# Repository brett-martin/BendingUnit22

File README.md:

# Bending Unit 22

BU-22 is a modular animatronic Bender-inspired clock and character display.
The Brain orchestrates operating modes, sensors, time, audio, and user input.
Independent Eyes and Mouth controllers own their LED hardware, rendering, and
precisely timed local animations.

This repository currently contains the proven Brain/Eyes breadboard tests,
draft display protocol, experimental content catalogs, and first clean v0
CircuitPython firmware slice.

## Repository map

```text
BU22_Brain/
  firmware/v0/          First Brain protocol exerciser
  tests/                Feather smoke test and reusable I2C validation suite

BU22_Eyes/
  catalogs/             Experimental expressions, animations, performances
  firmware/v0/          First clean Eyes firmware slice
  tests/                Universal I2C receiver and hardware-test backups

BU22_Mouth/
  README.md             Mouth subsystem placeholder

protocol/
  semantic_protocol_v0.md   Behavior, terminology, and ownership
  wire_protocol_v0.md       Concrete draft I2C encoding
  commands.md               Raw breadboard-only validation bytes
```

The original six-channel electrical bring-up programs are preserved under the
named Brain and Eyes test folders rather than serving as production firmware.

## Current breadboard hardware

- Adafruit Feather RP2040 acting as Brain
- Adafruit KB2040 acting as Eyes controller
- Six independent four-pixel SK9822 strands
- Three 74AHCT125 level-shifter ICs
- Independent USB power for both MCUs during development
- External regulated 5 V for level shifters and LEDs
- Shared ground, SDA, and SCL
- 4.7k I2C pull-ups to the Brain's 3.3 V rail
- Qwiic red power conductor disconnected during independent USB testing

### Eyes channel pin map

| Channel | Data | Clock |
|---:|---:|---:|
| 1 | D2 | D3 |
| 2 | D4 | D5 |
| 3 | D6 | D7 |
| 4 | D8 | D9 |
| 5 | D10 | A0 |
| 6 | A1 | A2 |

The current test assembly is physically rotated 180 degrees. Firmware keeps
content in logical orientation and applies the hardware transform at render
time.

## Proven functionality

- I2C discovery at Eyes address `0x30`
- One-byte and parameterized multi-byte commands
- Global brightness control
- Independent six-channel and 24-pixel control
- Complete 25-byte frame streaming at 10 FPS with no late frames
- Bidirectional status readback under display traffic
- Locally stored expressions and animations
- Immediate Brain interruption and STOP
- Dedicated Visor Down/Up row transitions
- Brain and Eyes disconnect/reconnect recovery
- Five-second standalone Normal fallback
- Visible missing-content development errors
- Concise action-level Eyes serial logging

See [the I2C validation index](BU22_Brain/tests/i2c_validation/README.md)
for the reusable development-board test sequence.

## Content catalogs

Expressions, animations, and performances use separate numeric ID spaces.
They remain experimental before v1. At v1, reviewed IDs become stable; later
content is appended while existing entries may improve without changing their
semantic meaning.

See [the Eyes catalog rules](BU22_Eyes/catalogs/README.md).

## Protocol documents

- [Semantic protocol v0](protocol/semantic_protocol_v0.md)
- [Wire protocol v0](protocol/wire_protocol_v0.md)
- [Raw hardware-validation commands](protocol/commands.md)

The semantic and wire documents are drafts. The raw validation bytes remain
separate so future hardware can rerun today's proven tests regardless of how
the production protocol evolves.

## Running the v0 Brain/Eyes slice

On the KB2040 Eyes `CIRCUITPY` drive, copy:

```text
BU22_Eyes/firmware/v0/code.py
BU22_Eyes/firmware/v0/config.py
BU22_Eyes/firmware/v0/content.py
```

Its `lib` directory also needs:

```text
adafruit_dotstar.mpy
adafruit_pixelbuf.mpy
```

On the Feather RP2040 Brain `CIRCUITPY` drive, copy:

```text
BU22_Brain/firmware/v0/code.py
```

The exerciser cycles expressions and animations, interrupts an animation,
tests Off and visor transitions, requests missing animation `999`, reads the
error status, and recovers with Normal.

## CircuitPython dependencies

Install the DotStar CircuitPython dependencies with:

```sh
python3 -m circup install -r requirements.txt
```

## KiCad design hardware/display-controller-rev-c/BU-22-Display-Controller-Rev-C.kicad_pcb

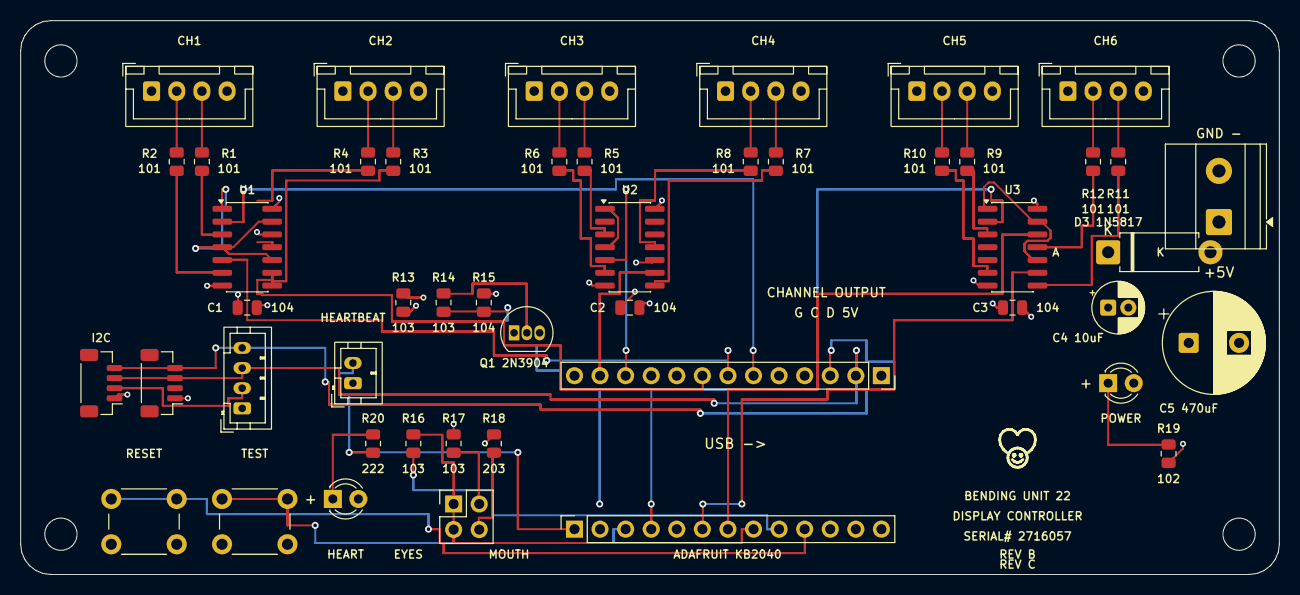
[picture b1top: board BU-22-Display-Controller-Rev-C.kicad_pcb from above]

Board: 4 copper layers, 125.0 x 55.0 mm, 52 parts (0 on the bottom side), 52 nets.

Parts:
C1, C2, C3: 100nF; C_0805_2012Metric
C4: 10uF; CP_Radial_D5.0mm_P2.00mm
C5: 470uF; CP_Radial_D10.0mm_P5.00mm
D1: GREEN POWER; LED_D3.0mm
D2: RED HEARTBEAT; LED_D3.0mm
D3: 1N5817 LOGIC ISOLATION; D_DO-15_P10.16mm_Horizontal
H1, H2, H3, H4: M3; MountingHole_3.2mm_M3
J1: CH1; JST_XH_B4B-XH-A_1x04_P2.50mm_Vertical
J2: CH2; JST_XH_B4B-XH-A_1x04_P2.50mm_Vertical
J3: CH3; JST_XH_B4B-XH-A_1x04_P2.50mm_Vertical
J4: CH4; JST_XH_B4B-XH-A_1x04_P2.50mm_Vertical
J5: CH5; JST_XH_B4B-XH-A_1x04_P2.50mm_Vertical
J6: CH6; JST_XH_B4B-XH-A_1x04_P2.50mm_Vertical
J7: 5V INPUT; TerminalBlock_Phoenix_MKDS-1,5-2-5.08_1x02_P5.08mm_Horizont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
J8: I2C TO BRAIN; JST_SH_BM04B-SRSS-TB_1x04-1MP_P1.00mm_Vertical
J9: I2C THRU; JST_SH_BM04B-SRSS-TB_1x04-1MP_P1.00mm_Vertical
J10: I2C TEST; JST_PH_B4B-PH-K_1x04_P2.00mm_Vertical
J11: GND HEARTBEAT; JST_PH_B2B-PH-K_1x02_P2.00mm_Vertical
JP1: ADDRESS; PinHeader_2x02_P2.54mm_Vertical
MCU1A: KB2040 ROW A; PinSocket_1x13_P2.54mm_Vertical
MCU1B: KB2040 ROW B; PinSocket_1x13_P2.54mm_Vertical
Q1: 2N3904 OE; TO-92_Inline
R1, R3, R5, R7, R9, R11: 100R DATA; R_0805_2012Metric
R2, R4, R6, R8, R10, R12: 100R CLOCK; R_0805_2012Metric
R13, R14, R16, R17: 10k; R_0805_2012Metric
R15: 100k; R_0805_2012Metric
R18: 20k; R_0805_2012Metric
R19: 1k; R_0805_2012Metric
R20: 2k2; R_0805_2012Metric
SW1: TEST; SW_PUSH_6mm
SW2: RESET; SW_PUSH_6mm
U1, U2, U3: 74AHCT125D; SOIC-14_3.9x8.7mm_P1.27mm

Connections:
3V3_LOCAL: MCU1A.9, R16.1
+5V: C1.1, C2.1, C3.1, C4.1, C5.1, J1.4, J2.4, J3.4, J4.4, J5.4, J6.4, J7.1, MCU1A.12, R13.1, R19.1, U1.14, U2.14, U3.14
ADDRESS: JP1.1, JP1.3, MCU1A.8, R16.2
ADDR_A0: JP1.2, R17.1
ADDR_A1: JP1.4, R18.1
CH1_CLOCK_3V3: MCU1B.7, U1.5
CH1_CLOCK_5V: R2.1, U1.6
CH1_CLOCK_OUT: J1.2, R2.2
CH1_DATA_3V3: MCU1B.6, U1.2
CH1_DATA_5V: R1.1, U1.3
CH1_DATA_OUT: J1.3, R1.2
CH2_CLOCK_3V3: MCU1B.9, U1.12
CH2_CLOCK_5V: R4.1, U1.11
CH2_CLOCK_OUT: J2.2, R4.2
CH2_DATA_3V3: MCU1B.8, U1.9
CH2_DATA_5V: R3.1, U1.8
CH2_DATA_OUT: J2.3, R3.2
CH3_CLOCK_3V3: MCU1B.11, U2.5
CH3_CLOCK_5V: R6.1, U2.6
CH3_CLOCK_OUT: J3.2, R6.2
CH3_DATA_3V3: MCU1B.10, U2.2
CH3_DATA_5V: R5.1, U2.3
CH3_DATA_OUT: J3.3, R5.2
CH4_CLOCK_3V3: MCU1B.13, U2.12
CH4_CLOCK_5V: R8.1, U2.11
CH4_CLOCK_OUT: J4.2, R8.2
CH4_DATA_3V3: MCU1B.12, U2.9
CH4_DATA_5V: R7.1, U2.8
CH4_DATA_OUT: J4.3, R7.2
CH5_CLOCK_3V3: MCU1A.5, U3.5
CH5_CLOCK_5V: R10.1, U3.6
CH5_CLOCK_OUT: J5.2, R10.2
CH5_DATA_3V3: MCU1A.4, U3.2
CH5_DATA_5V: R9.1, U3.3
CH5_DATA_OUT: J5.3, R9.2
CH6_CLOCK_3V3: MCU1A.7, U3.12
CH6_CLOCK_5V: R12.1, U3.11
CH6_CLOCK_OUT: J6.2, R12.2
CH6_DATA_3V3: MCU1A.6, U3.9
CH6_DATA_5V: R11.1, U3.8
CH6_DATA_OUT: J6.3, R11.2
ENABLE_BASE: Q1.2, R14.2
ENABLE_GPIO: MCU1A.2, R14.1, R15.1
GND: C1.2, C2.2, C3.2, C4.2, C5.2, D1.2, D2.2, J1.1, J2.1, J3.1, J4.1, J5.1, J6.1, J7.2, J8.1, J9.1, J10.1, J11.1, MCU1A.11, MCU1B.4, MCU1B.5, Q1.1, R15.2, R17.2, R18.2, SW1.2, SW2.2, U1.7, U2.7, U3.7
HEARTBEAT: J11.2, MCU1A.1, R20.1
HEART_LED_A: D2.1, R20.2
OE_N: Q1.3, R13.2, U1.1, U1.4, U1.10, U1.13, U2.1, U2.4, U2.10, U2.13, U3.1, U3.4, U3.10, U3.13
PWR_LED_A: D1.1, R19.2
RESET: MCU1A.10, SW2.1
SCL: J8.4, J9.4, J10.4, MCU1B.3
SDA: J8.3, J9.3, J10.3, MCU1B.2
TEST: MCU1A.3, SW1.1

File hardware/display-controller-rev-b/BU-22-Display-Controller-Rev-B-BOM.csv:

Category,References,Qty per board,Qty for 2 boards,Recommended purchase qty,Value / description,PCB footprint,Preferred manufacturer part,DigiKey part / search note,Status / notes
Logic,"U1,U2,U3",3,6,8,"74AHCT125 quad non-inverting buffer, active-low OE, 4.5-5.5V","SOIC-14, 3.9mm body, 1.27mm pitch",74AHCT125S14-13,31-74AHCT125S14-13CT-ND,"Use AHCT; do not substitute HC. Buy cut tape."
Transistor,Q1,1,2,5,"2N3904 NPN; pins 1=E, 2=B, 3=C",TO-92 inline,P2N3904BU,"Search P2N3904BU or equivalent E-B-C TO-92","Verify E-B-C lead order against the footprint."
Resistor,"R1-R12",12,24,30,"100 ohm, 1%, >=0.125W","0805 / 2012 metric",Generic,"Search 100 ohm 0805 1% thick film","Silkscreen code 101."
Resistor,"R13,R14,R16,R17",4,8,10,"10 kohm, 1%, >=0.125W","0805 / 2012 metric",Generic,"Search 10 kohm 0805 1% thick film","Silkscreen code 103."
Resistor,R15,1,2,5,"100 kohm, 1%, >=0.125W","0805 / 2012 metric",Generic,"Search 100 kohm 0805 1% thick film","Silkscreen code 104."
Resistor,R18,1,2,5,"20 kohm, 1%, >=0.125W","0805 / 2012 metric",Generic,"Search 20 kohm 0805 1% thick film","Silkscreen code 203."
Resistor,R19,1,2,5,"1 kohm, 1%, >=0.125W","0805 / 2012 metric",Generic,"Search 1 kohm 0805 1% thick film","Silkscreen code 102."
Resistor,R20,1,2,5,"2.2 kohm, 1%, >=0.125W","0805 / 2012 metric",Generic,"Search 2.2 kohm 0805 1% thick film","Silkscreen code 222."
Ceramic capacitor,"C1,C2,C3",3,6,10,"100 nF, X7R, >=16V","0805 / 2012 metric",Generic,"Search 0.1uF 0805 X7R 25V","Local bypass capacitors; silkscreen code 104."
Electrolytic capacitor,C4,1,2,5,"10 uF, >=16V, radial","5mm diameter, 2.0mm lead pitch",Generic,"Search 10uF 16V radial 5mm diameter 2mm pitch","Polarized; match diameter and pitch."
Electrolytic capacitor,C5,1,2,5,"470 uF, >=10V (16V preferred), radial","10mm diameter, 5.0mm lead pitch",Generic,"Search 470uF 16V radial 10mm diameter 5mm pitch","Polarized bulk capacitor."
LED,D1,1,2,5,"Green diffused LED, 3mm, standard current",3mm THT LED,Generic,"Search green diffused 3mm through-hole LED","Pin 1/anode is marked + on PCB."
LED,D2,1,2,5,"Red diffused LED, 3mm, standard current",3mm THT LED,Generic,"Search red diffused 3mm through-hole LED","Pin 1/anode is marked + on PCB."
Pushbutton,"SW1,SW2",2,4,6,"Momentary normally-open tactile switch, 6x6mm",KiCad SW_PUSH_6mm,Generic,"Search 6mm tactile switch through-hole; Adafruit 1009 style","Verify the common 6.5x4.5mm four-leg footprint."
Channel connector,"J1-J6",6,12,0,"JST XH vertical, 4 positions, 2.50mm",JST XH B4B vertical,B4B-XH-A,455-B4B-XH-A-ND,"Already owned: 24 pieces."
I2C connector,"J8,J9",2,4,5,"JST SH/Qwiic vertical SMD, 4 positions, 1.00mm",JST SH BM04B vertical SMD,BM04B-SRSS-TB,455-BM04B-SRSS-TBCT-ND,"J9 intentionally has no 3.3V output connection."
I2C test connector,J10,1,2,3,"JST PH vertical, 4 positions, 2.00mm",JST PH B4B vertical,B4B-PH-K-S,455-1706-ND,"Pins: GND, 3V3, SDA, SCL."
Heartbeat connector,J11,1,2,3,"JST PH vertical, 2 positions, 2.00mm",JST PH B2B vertical,B2B-PH-K-S,455-1704-ND,"Pins: GND, heartbeat input."
Address header,JP1,1,2,3,"2x2 male pin header, 2.54mm pitch",2x2 THT vertical header,Generic,"Search 2x2 2.54mm male header","Also buy two 2.54mm shunts per board."
MCU sockets,"MCU1A,MCU1B",2,4,6,"1x13 female socket, 2.54mm pitch",1x13 THT vertical socket,Generic,"Search 1x13 2.54mm female header/socket","Two socket rows per board; KB2040 is removable."
MCU,MCU1,1,2,0,"Adafruit KB2040 with male headers",Removable module,Adafruit KB2040,"User supplied","Not soldered directly to PCB."
Power terminal,J7,1,2,0,"2-position 5.08mm screw terminal",Phoenix MKDS-style 5.08mm,User supplied,"User supplied","Verify existing terminal has 5.08mm pin pitch."
Mechanical,"H1-H4",4,8,8,"M3 mounting hardware; 3.2mm NPTH",Mechanical hole,Generic,"M3 screws/standoffs as required","No electrical component installed."

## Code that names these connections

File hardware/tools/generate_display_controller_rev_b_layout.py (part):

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    text(board, "REV B", 99.0, 53.0, 0.8)

    names = {"+5V", "GND", "3V3_LOCAL", "3V3_BRAIN", "SDA", "SCL",
             "HEARTBEAT", "ADDRESS", "TEST", "RESET", "ENABLE_GPIO",
             "ENABLE_BASE", "OE_N", "PWR_LED_A", "HEART_LED_A",
             "ADDR_A0", "ADDR_A1"}
    for ch in range(1, 7):
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                      f"CH{ch}_DATA_OUT", f"CH{ch}_CLOCK_OUT"})
    nets = {name: net(board, name) for name in sorted(names)}

    top = {1: "HEARTBEAT", 2: "ENABLE_GPIO", 3: "TEST",
           4: "CH5_DATA_3V3", 5: "CH5_CLOCK_3V3", 6: "CH6_DATA_3V3",
           7: "CH6_CLOCK_3V3", 8: "ADDRESS", 9: "3V3_LOCAL",
           10: "RESET", 11: "GND", 12: "+5V"}
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    for ref, pin, name in (
        ("Q1", 1, "GND"), ("Q1", 2, "ENABLE_BASE"), ("Q1", 3, "OE_N"),
        ("R13", 1, "+5V"), ("R13", 2, "OE_N"),
        ("R14", 1, "ENABLE_GPIO"), ("R14", 2, "ENABLE_BASE"),
        ("R15", 1, "ENABLE_GPIO"), ("R15", 2, "GND"),
        ("R16", 1, "3V3_LOCAL"), ("R16", 2, "ADDRESS"),
        ("R17", 1, "ADDR_A0"), ("R17", 2, "GND"),
        ("R18", 1, "ADDR_A1"), ("R18", 2, "GND"),
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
